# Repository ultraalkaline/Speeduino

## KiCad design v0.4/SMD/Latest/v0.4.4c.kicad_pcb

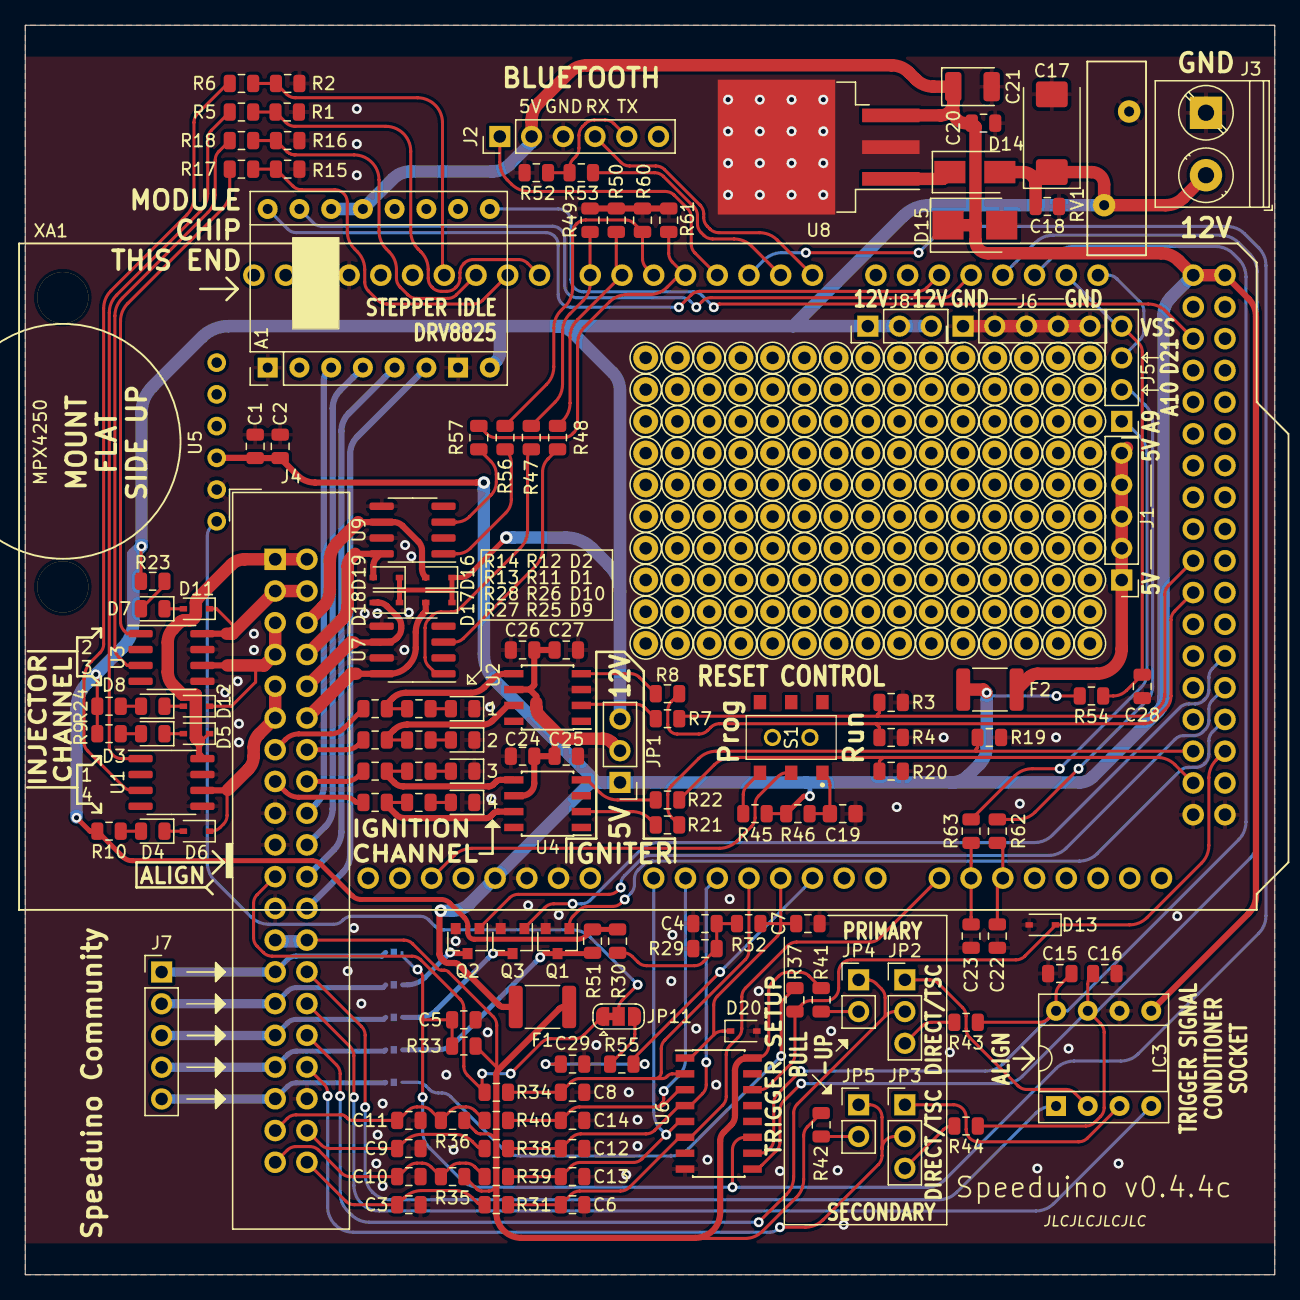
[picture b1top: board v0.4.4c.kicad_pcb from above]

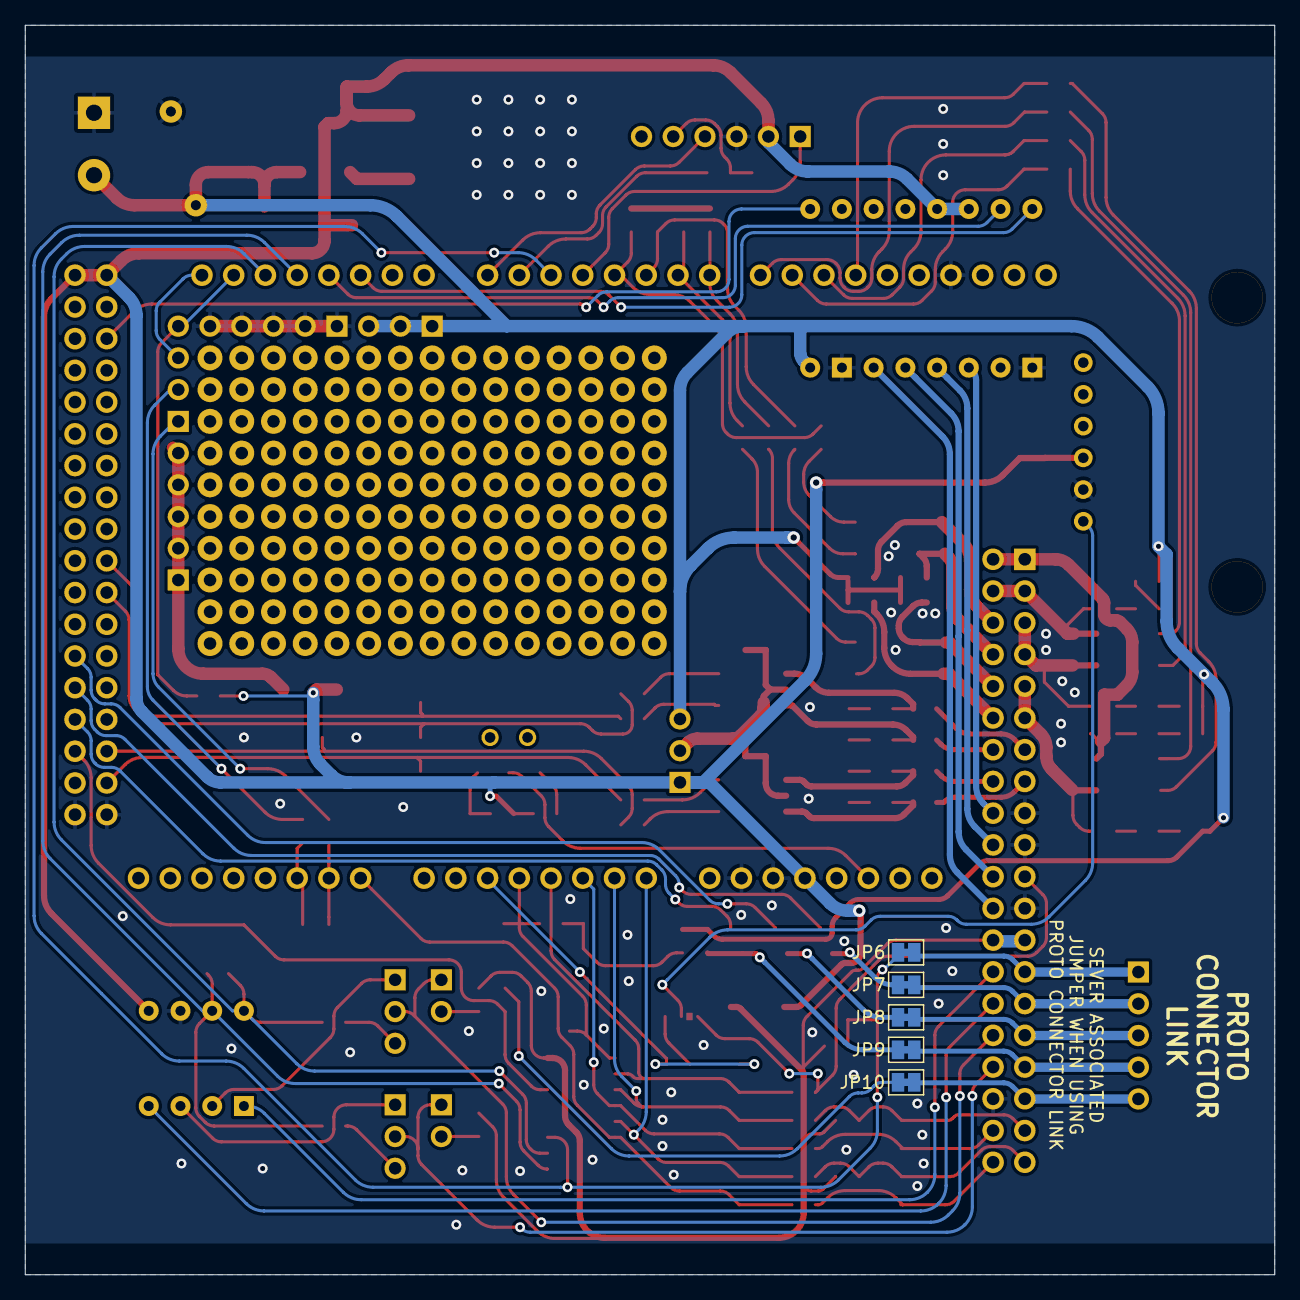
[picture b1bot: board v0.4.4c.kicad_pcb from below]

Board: 2 copper layers, 100.0 x 100.0 mm, 148 parts (5 on the bottom side), 120 nets.

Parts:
A1: Pololu_Breakout_DRV8825; Pololu_Breakout-16_15.2x20.3mm
C1, C15: 0.01uF; C_0805_2012Metric
C2, C25, C27: 1uF; C_0805_2012Metric
C3, C4, C9, C10, C11, C16, C18, C20, C22, C23, C24, C26, C28: 0.1uF; C_0805_2012Metric
C5, C6, C7, C12, C13, C14: 0.22uF; C_0805_2012Metric
C8, C29: 470pf; C_0805_2012Metric
C17: 10uF; CP_EIA-7343-31_Kemet-D
C19: 22uF; C_0805_2012Metric_Pad1.15x1.40mm_HandSolder
C21: 47uF; CP_EIA-3528-21_Kemet-B
D1, D2, D3, D4, D7, D8, D9, D10: LED; LED_0805_2012Metric
D5, D6, D11, D12, D16, D17, D18, D19: D; D_SOD-323
D13, D20: D_Zener; D_SOD-323
D14: B130-13-F; D_SMA
D15: 1SMB5919BT3G; D_SMB
F1, F2: Polyfuse; Fuse_1812_4532Metric
IC3: Trig Cond Socket; DIP-8_W7.62mm_Socket
J1, J6, J7: Conn_01x05; PinHeader_1x05_P2.54mm_Vertical
J2: Conn_01x06; PinHeader_1x06_P2.54mm_Vertical
J3: Conn_01x02; TerminalBlock_Phoenix_PT-1,5-2-5.0-H_1x02_P5.00mm_Horizontal
J4: Conn_02x20_Counter_Clockwise; IDC-Header_2x20_P2.54mm_Vertical
J5: Conn_01x04; PinHeader_1x04_P2.54mm_Vertical
J8: Conn_01x03; PinHeader_1x03_P2.54mm_Vertical
JP1: Ignition Voltage; PinHeader_1x03_P2.54mm_Vertical
JP2, JP3: VR-HALL; PinHeader_1x03_P2.54mm_Vertical
JP4, JP5: PULL-UP; PinHeader_1x02_P2.54mm_Vertical
JP6, JP7, JP8, JP9, JP10: SolderJumper_2_Bridged; SolderJumper-2_P1.3mm_Bridged_Pad1.0x1.5mm
JP11: Jumper_3_Bridged12; SolderJumper-3_P1.3mm_Bridged12_RoundedPad1.0x1.5mm
Q1, Q2, Q3: SSM3K357R; SOT-23
R1, R2, R3, R4, R15, R16, R19, R20, R49, R50, R60, R61: 100k; R_0805_2012Metric
R5, R6, R7, R8, R17, R18, R21, R22, R29, R37, R41, R42, R47, R48, R53, R54, R56, R57: 1k; R_0805_2012Metric
R9, R10, R11, R12, R23, R24, R25, R26, R33: 2.4k; R_0805_2012Metric
R13, R14, R27, R28: 10R; R_0805_2012Metric
R30: 3.9k; R_0805_2012Metric
R31, R32, R34, R38, R39, R40, R55, R62, R63: 470R; R_0805_2012Metric
R35, R36: 2.49k; R_0805_2012Metric
R43, R44: 220R; R_0805_2012Metric
R45, R51: 10k; R_0805_2012Metric
R46: 120R; R_0805_2012Metric
R52: 2k; R_0805_2012Metric
RV1: Varistor; RV_Disc_D15.5mm_W4.7mm_P7.5mm
S1: AYZ0202AGRLC
U1, U3, U7, U9: VNLD5090; SOIC-8_3.9x4.9mm_P1.27mm
U2, U4: TC4424A; SOIC-8_3.9x4.9mm_P1.27mm
U5: MPX4250
U6: SP720; SOIC-16_3.9x9.9mm_P1.27mm
U8: LM2940S-5.0/NOPB; TO-263-3_TabPin2
XA1: Arduino_Mega2560_Shield; Arduino_Mega2560_Shield_IO_Only

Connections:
12V-SW: A1.8, C17.1, C18.1, D14.2, D16.1, D17.1, D18.1, D19.1, J3.2, J8.1, J8.2, J8.3, JP1.3, R9.2, R10.2, R23.2, R24.2, R30.2, R51.2, RV1.1
ADC-Clamp-1: C7.1, D20.1, R32.1, U6.1, XA1.A4
ADC-Clamp-2: C8.2, R34.1, U6.2, XA1.A3
ADC-Clamp-3: C14.1, R40.1, U6.3, XA1.A1
ADC-Clamp-4: C12.1, R38.1, U6.4, XA1.A2
ADC-Clamp-5: C13.1, R39.1, U6.5, XA1.A0
ADC-Clamp-6: C6.1, R31.1, U6.6, XA1.A8
ADC-Clamp-8: C16.2, IC3.7, R44.1, U6.9, XA1.D18
ADC-Clamp-9: C15.2, IC3.8, R43.1, U6.10, XA1.D19
ADC-Clamp-10: C5.1, JP6.1, R33.2, U6.11, XA1.D2
ADC-Clamp-13: D13.1, R37.2, U6.14, XA1.D51
BOOST-OUT: D17.2, J4.12, U7.8
CAM-IN: J4.34, JP3.2, JP5.1
CLT_Sensor: C11.1, J4.37, R36.1, R40.2
CRANK-IN: J4.32, JP2.2, JP4.1
Clutch_in: JP10.1, R37.1
FAN-OUT: JP7.1, Q2.3
FUELPUMP-OUT: JP8.1, Q3.3
GND: A1.1, A1.7, C1.1, C2.1, C3.2, C4.2, C5.2, C6.2, C7.2, C8.1, C9.2, C10.2, C11.2, C12.2, C13.2, C14.2, C15.1, C16.1, C17.2, C18.2, C19.2, C20.2, C21.2, C22.2, C23.2, C24.1, C25.1, C26.1, C27.1, C28.1, C29.2, D1.1, D2.1, D9.1, D10.1, D13.2, D15.2, D20.2, IC3.6, J2.3, J3.1, J4.17, J4.19, J4.23, J4.36, J6.1, J6.2, J6.3, J6.4, J6.5, Q1.2, Q2.2, Q3.2, R1.2, R2.1, R3.2, R4.1, R15.2, R16.1, R19.2, R20.1, R29.1, R49.2, R50.1, R52.2, R60.2, R61.1, RV1.2, U1.5, U1.7, U2.3, U3.5, U3.7, U4.3, U5.2, U6.8, U7.5, U7.7, U8.2, U9.5, U9.7, XA1.GND1, XA1.GND2, XA1.GND3, XA1.GND5, XA1.GND6
HC-1-OUT: D18.2, J4.10, U7.6
HC-2-OUT: D16.2, J4.6, U9.6
IAT_Sensor: C10.1, J4.39, R35.1, R39.2
IDLE-OUT: D19.2, J4.8, U9.8
IGN-1-OUT: J4.13, R14.1
IGN-2-OUT: J4.14, R13.1
IGN-3-OUT: J4.16, R28.1
IGN-4-OUT: J4.15, R27.1
INJ-1-OUT: D5.1, J4.1, J4.2, U1.8
INJ-2-OUT: D11.1, J4.3, J4.4, U3.8
INJ-3-OUT: D12.1, J4.5, J4.7, U3.6
INJ-4-OUT: D6.1, J4.9, J4.11, U1.6
MAP-EXT: J4.21, JP11.1, R34.2
MCU-A5: C29.1, R55.1, XA1.A5
MCU-A9: C23.1, R63.1, XA1.A9
MCU-A10: C22.1, R62.2, XA1.A10
MCU-D0: J2.4, XA1.D0
MCU-D1: R53.1, XA1.D1
MCU-D3: J2.1, XA1.D3
MCU-D4: R57.2, R61.2, XA1.D4
MCU-D5: R56.2, R60.1, XA1.D5
MCU-D6: R48.2, R50.2, XA1.D6
MCU-D7: R47.2, R49.1, XA1.D7
MCU-D8: R1.1, R5.2, XA1.D8
MCU-D9: R15.1, R17.2, XA1.D9
MCU-D10: R16.2, R18.2, XA1.D10
MCU-D11: R2.2, R6.2, XA1.D11
MCU-D16: A1.16, XA1.D16
MCU-D17: A1.15, XA1.D17
MCU-D20: C28.2, J5.4, R54.1, XA1.D20
MCU-D21: J5.3, XA1.D21
MCU-D24: A1.9, XA1.D24
MCU-D38: R3.1, R7.2, XA1.D38
MCU-D40: R4.2, R8.2, XA1.D40
MCU-D45: Q3.1, XA1.D45
MCU-D47: Q2.1, XA1.D47
MCU-D49: Q1.1, XA1.D49
MCU-D50: R19.1, R21.2, XA1.D50
MCU-D52: R20.2, R22.2, XA1.D52
unnamed: C4.1, R29.2, R30.1, R32.2
unnamed: C19.1, R46.1, S1.1
unnamed: D1.2, R11.2
unnamed: D2.2, R12.2
unnamed: D3.1, D5.2
unnamed: D3.2, R9.1
unnamed: D4.1, D6.2
unnamed: D4.2, R10.1
unnamed: D7.2, R23.1
unnamed: D8.2, R24.1
unnamed: D9.2, R25.2
unnamed: D10.2, R26.2
unnamed: D7.1, D11.2
unnamed: D8.1, D12.2
unnamed: F2.2, J1.1, J1.2, J1.3, J1.4, J1.5
unnamed: IC3.2, JP2.1
unnamed: IC3.3, JP3.1
unnamed: J2.5, R52.1, R53.2
unnamed: J5.1, R63.2
unnamed: J5.2, R62.1
unnamed: JP2.3, R43.2
unnamed: JP3.3, R44.2
unnamed: JP4.2, R41.1
unnamed: JP5.2, R42.1
unnamed: JP11.2, U5.1
unnamed: JP11.3, R55.2
unnamed: R5.1, U1.1
unnamed: R6.1, U1.3
unnamed: R7.1, U2.2
unnamed: R8.1, U2.4
unnamed: R11.1, R13.2, U2.7
unnamed: R12.1, R14.2, U2.5
unnamed: R17.1, U3.1
unnamed: R18.1, U3.3
unnamed: R21.1, U4.2
unnamed: R22.1, U4.4
unnamed: R25.1, R27.2, U4.7
unnamed: R26.1, R28.2, U4.5
unnamed: R45.1, S1.3
unnamed: R47.1, U7.1
unnamed: R48.1, U7.3
unnamed: R56.1, U9.1
unnamed: R57.1, U9.3
O2_Sensor: C3.1, J4.40, R31.2
PROTO-1: J4.27, J7.1, JP6.2
PROTO-2: J4.29, J7.2, JP7.2
PROTO-3: J4.31, J7.3, JP8.2
PROTO-4: J4.33, J7.4, JP9.2
PROTO-5: J4.35, J7.5, JP10.2
RESET: S1.2, XA1.RST1
STEP-A1: A1.4, J4.20
STEP-A2: A1.3, J4.18
STEP-B1: A1.5, J4.22
STEP-B2: A1.6, J4.24
TACHO-OUT: JP9.1, Q1.3, R51.1
TPS_Sensor: C9.1, J4.38, R38.2
VDD: A1.13, A1.14, C1.2, C2.2, C20.1, C21.1, D15.1, F1.2, F2.1, IC3.5, J2.2, JP1.1, R45.2, R46.2, R54.2, U5.3, U8.3, XA1.5V1, XA1.5V3, XA1.5V4
VDDA: F1.1, J4.25, J4.26, R33.1, R35.2, R36.2, R41.2, R42.2, U6.16
VR1-: IC3.1, J4.28
VR2-: IC3.4, J4.30
VRegIn: D14.1, U8.1
Vdrive: C24.2, C25.2, C26.2, C27.2, JP1.2, U2.6, U4.6

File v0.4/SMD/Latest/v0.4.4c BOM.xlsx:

Designator | Quantity | Value | Footprint | Manufacturer | Mfr. Part # | URL
C1 C15 | 2 | 0.01uF | Capacitor_SMD:C_0805_2012Metric | Yageo | CC0805KRX7R9BB103 | https://www.digikey.com/product-detail/en/yageo/CC0805KRX7R9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
C17 | 1 | 10uF | Capacitor_Tantalum_SMD:CP_EIA-7343-31_Kemet-D | Kemet | T491D106K050AT | https://www.digikey.com/product-detail/en/kemet/T491D106K050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
C19 | 1 | 22uF | Capacitor_SMD:C_0805_2012Metric_Pad1.15x1.40mm_HandSolder | Samsung | CL21A226KQCLRNC | https://www.digikey.com.au/product-detail/en/samsung-electro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
C21 | 1 | 47uF | Capacitor_Tantalum_SMD:CP_EIA-3528-21_Kemet-B | AVX | TAJB476K006RNJ | https://www.digikey.com/product-detail/en/avx-corporation/TA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
C24 C26 C3 C9 C10 C11 C4 C16 C18 C20 C23 C22 C28 | 13 | 0.1uF | Capacitor_SMD:C_0805_2012Metric | Yageo | CC0805KRX7R9BB104 | https://www.digikey.com.au/product-detail/en/yageo/CC0805KRX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
C25 C27 C2 | 3 | 1uF | Capacitor_SMD:C_0805_2012Metric | Yageo | CC0805KKX7R7BB105 | https://www.digikey.com/product-detail/en/yageo/CC0805KKX7R7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
C6 C12 C13 C14 C7 C5 | 6 | 0.22uF | Capacitor_SMD:C_0805_2012Metric | Samsung | CL21B224KOCNNNC | https://www.digikey.com/product-detail/en/samsung-electro-me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
C8 C29 | 2 | 470pf | Capacitor_SMD:C_0805_2012Metric | Yageo | CC0805KRX7R9BB471 | https://www.digikey.com/product-detail/en/yageo/CC0805KRX7R9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
D12 D11 D5 D6 D18 D17 D19 D16 | 8 | D | Diode_SMD:D_SOD-323 | MCC | 1N4448WX-TP | https://www.digikey.com/product-detail/en/micro-commercial-c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
D13 D20 | 2 | D_Zener | Diode_SMD:D_SOD-323 | On Semi | MM3Z5V1ST1G | https://www.digikey.com/product-detail/en/on-semiconductor/M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
D14 | 1 | B130-13-F | Diode_SMD:D_SMA | Diodes Inc | B130-13-F | https://www.digikey.com.au/product-detail/en/diodes-incorpor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
D15 | 1 | 1SMB5919BT3G | Diode_SMD:D_SMB | On Semi | 1SMB5919BT3G | https://www.digikey.com.au/product-detail/en/on-semiconducto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
D4 D3 D8 D7 D1 D2 D9 D10 | 8 | LED | LED_SMD:LED_0805_2012Metric | Osram | LH R974-LP-1 | https://www.digikey.com/product-detail/en/osram-opto-semicon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
F1 F2 | 2 | Polyfuse | Fuse:Fuse_1812_4532Metric | Bel Fuse | 0ZCC0050FF2C | https://www.digikey.com.au/product-detail/en/bel-fuse-inc/0Z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
IC3 | 2 | Trig Cond Socket | Package_DIP:DIP-8_W7.62mm_Socket | Sullins Connector Solutions | PPTC041LFBN-RC | https://www.digikey.com.au/product-detail/en/sullins-connect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
J3 | 1 | Conn_01x02 | TerminalBlock_Phoenix:TerminalBlock_Phoenix_PT-1,5-2-5.0-H_1x02_P5.00mm_Horizon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 | TE | 282836-2 | https://www.digikey.com.au/product-detail/en/te-connectivity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
J4 | 1 | Conn_02x20_Counter_Clockwise | Connector_IDC:IDC-Header_2x20_P2.54mm_Vertical | CNC Tech | 571-5103308-8 | https://www.digikey.com.au/products/en?keywords=1175-1614-ND
JP1 | 1 | Ignition Voltage | Connector_PinHeader_2.54mm:PinHeader_1x03_P2.54mm_Vertical | Harwin Inc | M20-9990345 | https://www.digikey.com.au/products/en?keywords=M20-9990345
JP2 JP3 | 2 | VR-HALL | Connector_PinHeader_2.54mm:PinHeader_1x03_P2.54mm_Vertical | Harwin Inc | M20-9990345 | https://www.digikey.com.au/products/en?keywords=M20-9990345
JP5 JP4 | 2 | PULL-UP | Connector_PinHeader_2.54mm:PinHeader_1x02_P2.54mm_Vertical | Harwin Inc | M20-9990245 | https://www.digikey.com.au/products/en?keywords=M20-9990245
Q1 Q3 Q2 | 3 | SSM3K357R | Package_TO_SOT_SMD:SOT-23 | Toshiba | SSM3K357R | https://www.digikey.com.au/product-detail/en/toshiba-semicon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
R1 R2 R15 R16 R3 R4 R19 R20 R50 R49 R61 R60 | 12 | 100k | Resistor_SMD:R_0805_2012Metric | Yageo | RC0805FR-07100KL | https://www.digikey.com/product-detail/en/yageo/RC0805FR-071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
R10 R9 R24 R23 R11 R12 R25 R26 R33 | 9 | 2.4k | Resistor_SMD:R_0805_2012Metric | Yageo | RC0805FR-072K4L | https://www.digikey.com/product-detail/en/yageo/RC0805FR-072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
R13 R14 R27 R28 | 4 | 10R | Resistor_SMD:R_0805_2012Metric | Yageo | RC0805FR-0710RL | https://www.digikey.com/product-detail/en/yageo/RC0805FR-071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
R30 | 1 | 3.9k | Resistor_SMD:R_0805_2012Metric | Yageo | RC0805FR-073K9L | https://www.digikey.com/product-detail/en/yageo/RC0805FR-073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
R34 R31 R38 R39 R40 R32 R55 R63 R62 | 9 | 470R | Resistor_SMD:R_0805_2012Metric | Panasonic | ERJ-6ENF4700V | https://www.digikey.com/product-detail/en/panasonic-electron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
R35 R36 | 2 | 2.49k | Resistor_SMD:R_0805_2012Metric | Yageo | RT0805BRD072K49L | https://www.digikey.com/product-detail/en/yageo/RT0805BRD072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
R43 R44 | 2 | 220R | Resistor_SMD:R_0805_2012Metric | Yageo | RC0805FR-07220RL | https://www.digikey.com/product-detail/en/yageo/RC0805FR-072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
R45 R51 | 2 | 10k | Resistor_SMD:R_0805_2012Metric | Yageo | RC0805JR-0710KL | https://www.digikey.com/product-detail/en/yageo/RC0805JR-071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
R46 | 1 | 120R | Resistor_SMD:R_0805_2012Metric | Yageo | RC0805FR-07120RL | https://www.digikey.com/product-detail/en/yageo/RC0805FR-071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
R5 R6 R17 R18 R7 R8 R21 R22 R29 R37 R41 R42 R47 R48 R56 R57 R53 R54 | 18 | 1k | Resistor_SMD:R_0805_2012Metric | Yageo | RC0805FR-071KL | https://www.digikey.com/product-detail/en/yageo/RC0805FR-071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
R52 | 1 | 2k | Resistor_SMD:R_0805_2012Metric | Yageo | RC0805FR-072KL | https://www.digikey.com/product-detail/en/yageo/RC0805FR-072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
RV1 | 1 | Varistor | Varistor:RV_Disc_D15.5mm_W4.7mm_P7.5mm | Bournes Inc | MOV-14D220K | https://www.digikey.com.au/product-detail/en/bourns-inc/MOV-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
S1 | 1 | AYZ0202AGRLC | Misc:AYZ0202AGRLC | C & K COMPONENTS | AYZ0202AGRLC | https://www.digikey.com.au/product-detail/en/c-k/AYZ0202AGRL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
U1 U3 U7 U9 | 4 | VNLD5090 | Package_SO:SOIC-8_3.9x4.9mm_P1.27mm | STMicro | VNLD5090-E | https://www.digikey.com.au/products/en?keywords=VNLD5090-E
U2 U4 | 2 | TC4424A | Package_SO:SOIC-8_3.9x4.9mm_P1.27mm | Microchip | TC4424AVOA | https://www.digikey.com/product-detail/en/microchip-technolo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
U5 | 1 | MPX4250 | Misc:MPX4250 | NXP | MPX4250AP | https://www.digikey.com.au/product-detail/en/nxp-usa-inc/MPX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
U6 | 1 | SP720 | Package_SO:SOIC-16_3.9x9.9mm_P1.27mm | Littelfuse | SP720ABTG | https://www.digikey.com/product-detail/en/littelfuse-inc/SP7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
U8 | 1 | LM2940S-5.0/NOPB | Package_TO_SOT_SMD:TO-263-3_TabPin2 | TI | LM2940S-5.0/NOPB | https://www.digikey.com.au/products/en?keywords=LM2940S-5.0%2FNOPB
XA1 | 4 | Arduino_Mega2560 header pins | CONN HEADER .100" SNGL STR 40POS | Sullins Connector Solutions | PREC040SAAN-RC | https://www.digikey.com.au/products/en?keywords=S1012EC-40-ND | Pins on underside of board

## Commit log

2023-03-22 Filled traces
2023-03-24 Completed fillet of tracks
2023-03-24 Removed KiCad backup folders and added them to .gitignore
2024-01-30 Fixed some issues with v0.4 (SMD)
